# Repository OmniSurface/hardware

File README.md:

This repo stores hardware design files and datasheets of components we used.

## Files
- `datasheet`: this folder stores datasheets of the ICs/sensors we used.
- `img`: pictures of circuit diagrams
- `kicad components`: stores schematic files and footprints of components
- `tlv2771 breakout`: an easy breakout board for the breadboard testing of the TLV2771 Operational Amplifier chip.
- `piezo_v1`: version 1 of the integrated circuit, including a piezo sensor, preamplification of the sensor reading, and a high sampling rate ADC circuit, which communicates with the MCU (ESP32S3) using the SPI interface.
- `mini_v1`: deleted ADC subcircuit and uses a dual channel amplifier (TLV2722) to amplify readings from both the piezo and bone conducting mic sensor. Uses CR2477 coin cell battery to power the ESP32S3 XIAO.
- `mini_lipo_v1`: same as the `mini_v1`, other than it uses a 30.0mm x 25.5mm x 7.1mm 500mAh lipo battery to power the ESP32S3 XIAO.
- `backup_microphone`: this file includes the testing for the backup plan, which is using microphone as the second sensor if piezo or bone conduction cannot work as expected.

## Circuit Diagrams
### Preamplifier 

- `Vcc` uses 3.3v from the ESP32S3.
- `Rb` = 10MOhm
- `Rg` = 1kOhm
- `Rf` = 56kOhm
- `Cf` is not used, since we want to keep the high-frequency signals.
- `1/2 Vcc` is created using a voltage divider (2 x 10kOhm resistor).

### ADC 

With some modifications:
- `IN+` of the ADC is connected to the `Vo` of the preamplifier.
- `IN-` of the ADC is connected to `1/2 Vcc`.
- `V+` line and the `VIO` are connected to the 3.3v from the ESP32S3.
- `VREF` = 3v. This means the ADC can convert voltage from -3v to 3v. In our configuration, however, we will only generate signals from -1/2 Vcc to 1/2 Vcc, which is around -1.65v to 1.65v. This will waste 1-bit resolution of the ADC as we only use half of the voltage range. Hope it could still be accurate enough, or we can develop a differential input for the ADC (rather than directly pulling 1/2 Vcc to the `IN-` of the ADC).

## Main Considerations
### Bandwidth
In our preliminary testing using o-scope, a gain of around 50x can produce a desirable signal for all kinds of surface interactions. The TLV2771 amplifier we used has a Gain Bandwidth (GBW) of 5.1 MHz. The formula to calculate the bandwidth of the op-amp when operating at a specific gain is given by:
\[ \text{Bandwidth} = \frac{\text{GBW}}{\text{Gain}} \]
Where,
    - Bandwidth is the frequency at which the gain of the op-amp falls to 1 (unity gain) when operating at a specific gain setting.
    - GBW (Gain-Bandwidth Product) is a characteristic of the op-amp and is usually specified in the datasheet. It's the product of the bandwidth and the gain at which the bandwidth is measured.
    - Gain is the amplification factor at which the op-amp is operating.

In our case, the gain is 50, then the bandwidth is around 100kHz, which could be sufficient in our case of interacting with surfaces.

If a higher GBW turns out to be necessary, we can use LMP7732, which has a GBW of __22MHz__.

### ADC sampling
The AD4022 chip we used for ADC has a maximum sampling rate of around 500kSPS. 

According to the Nyquist theorem, which states that to avoid aliasing, which is the distortion that occurs when the signal is undersampled, the sampling rate must be at least twice the highest frequency present in the signal. This minimum sampling rate is known as the Nyquist rate.
\[ f_{\text{Nyquist}} = 2 \times f_{\text{max}} \]
Where,
 - $f_{\text{max}}$ is the highest frequency component in the signal.

 Given the bandwidth of the preamplifier is 100kHz, our 500kHz sampling rate could be sufficient.

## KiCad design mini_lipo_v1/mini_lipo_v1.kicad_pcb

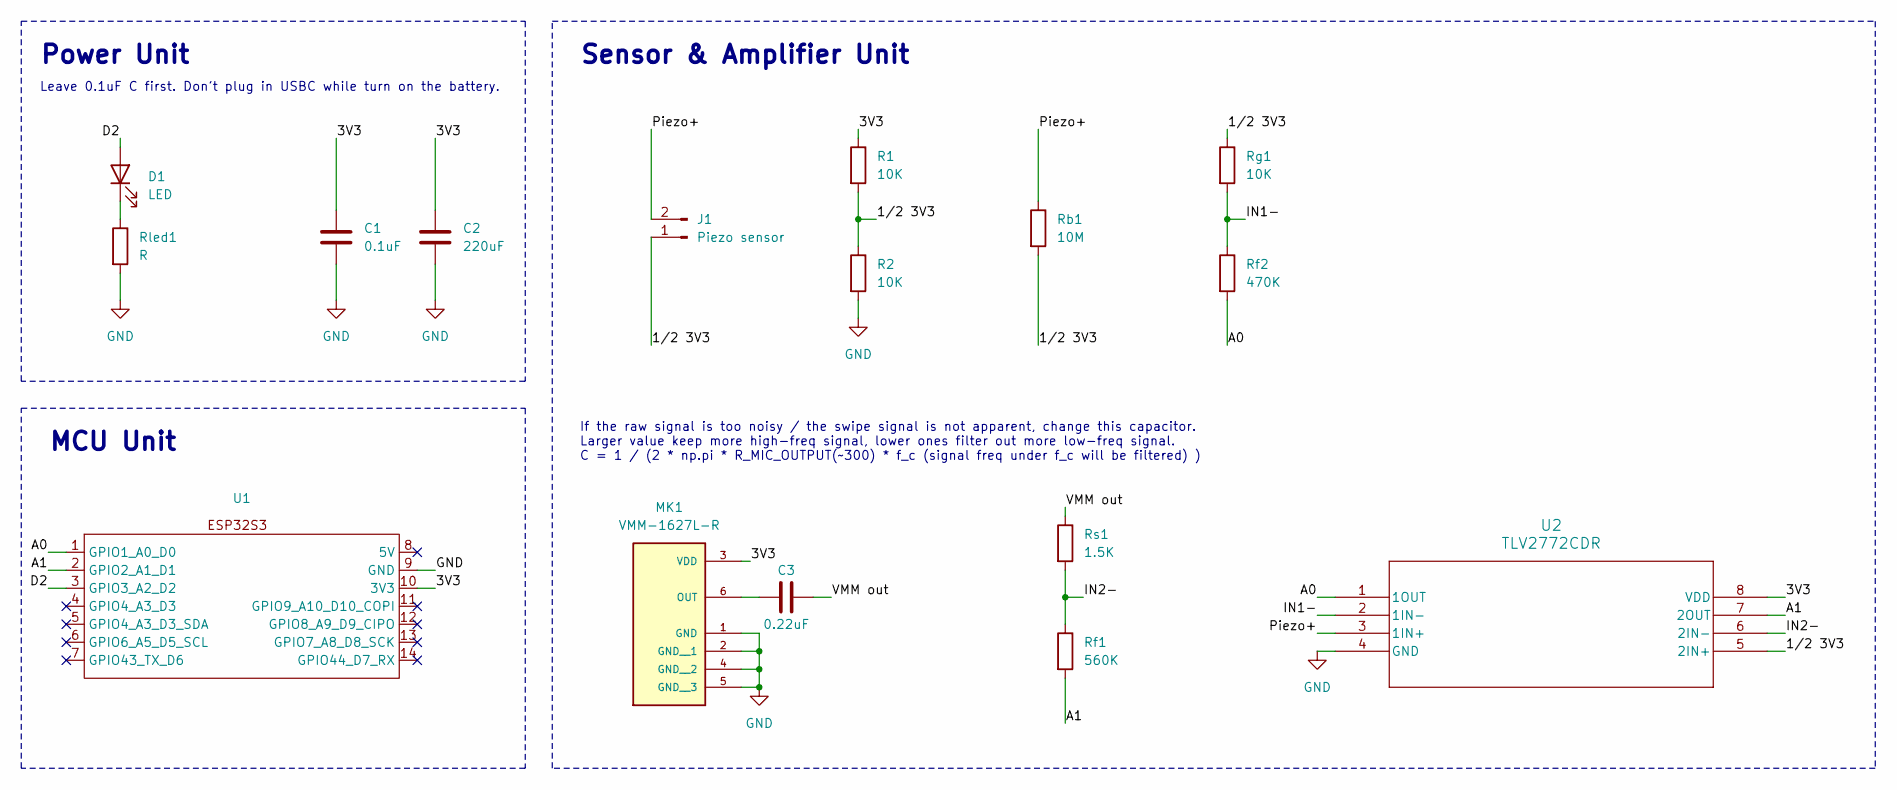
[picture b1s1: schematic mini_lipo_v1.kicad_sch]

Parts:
C1: 0.1uF; C_0805_2012Metric_Pad1.18x1.45mm_HandSolder
C2: 220uF; 300uF_laydown
C3: 0.22uF; C_0805_2012Metric_Pad1.18x1.45mm_HandSolder
D1: LED; LED_D3.0mm
J1: Piezo sensor; PinHeader_1x02_P2.54mm_Vertical
MK1: VMM-1627L-R; MIC_VMM-1627L-R; PARTREV A
R1, R2: 10K; R_0805_2012Metric_Pad1.20x1.40mm_HandSolder
Rb1: 10M; R_0805_2012Metric_Pad1.20x1.40mm_HandSolder
Rf1: 560K; R_0805_2012Metric_Pad1.20x1.40mm_HandSolder
Rf2: 470K; R_0805_2012Metric_Pad1.20x1.40mm_HandSolder
Rg1: 10K; R_0805_2012Metric_Pad1.20x1.40mm_HandSolder
Rled1: R; C_0805_2012Metric_Pad1.18x1.45mm_HandSolder
Rs1: 1.5K; R_0805_2012Metric_Pad1.20x1.40mm_HandSolder
U1: XIAO_SMD
U2: TLV2772CDR

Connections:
/1/2 3V3: J1.1, R1.2, R2.1, Rb1.2, Rg1.1, U2.5 (2IN+)
/3V3: C1.1, C2.1, MK1.3 (VDD), R1.1, U1.10 (3V3), U2.8 (VDD)
/A0: Rf2.2, U1.1 (GPIO1_A0_D0), U2.1 (1OUT)
/A1: Rf1.2, U1.2 (GPIO2_A1_D1), U2.7 (2OUT)
/D2: D1.2 (A), U1.3 (GPIO3_A2_D2)
/IN1-: Rf2.1, Rg1.2, U2.2 (1IN-)
/IN2-: Rf1.1, Rs1.2, U2.6 (2IN-)
/Piezo+: J1.2, Rb1.1, U2.3 (1IN+)
/VMM out: C3.2, Rs1.1
GND: C1.2, C2.2, MK1.1 (GND), MK1.2 (GND__1), MK1.4 (GND__2), MK1.5 (GND__3), R2.2, Rled1.2, U1.9 (GND), U2.4 (GND)
unnamed: D1.1 (K), Rled1.1
unnamed: C3.1, MK1.6 (OUT)

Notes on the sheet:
Power Unit
Sensor & Amplifier Unit
If the raw signal is too noisy / the swipe signal is not apparent, change this capacitor. Larger value keep more high-freq signal, lower ones filter out more low-freq signal. C = 1 / (2 * np.pi * R_MIC_OUTPUT(~300) * f_c (signal freq under f_c will be filtered) )
MCU Unit
Leave 0.1uF C first. Don't plug in USBC while turn on the battery.

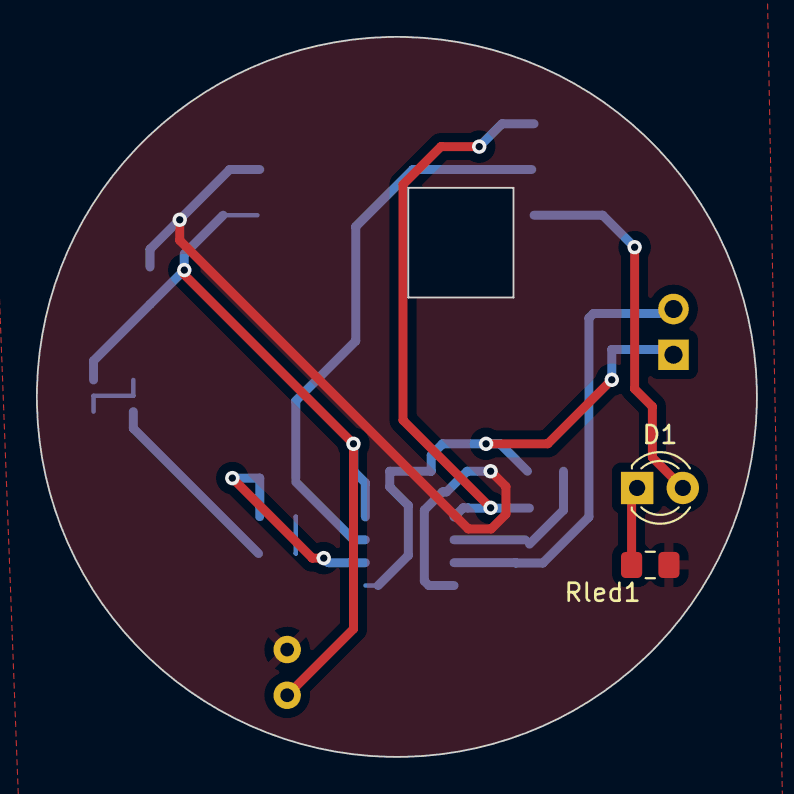
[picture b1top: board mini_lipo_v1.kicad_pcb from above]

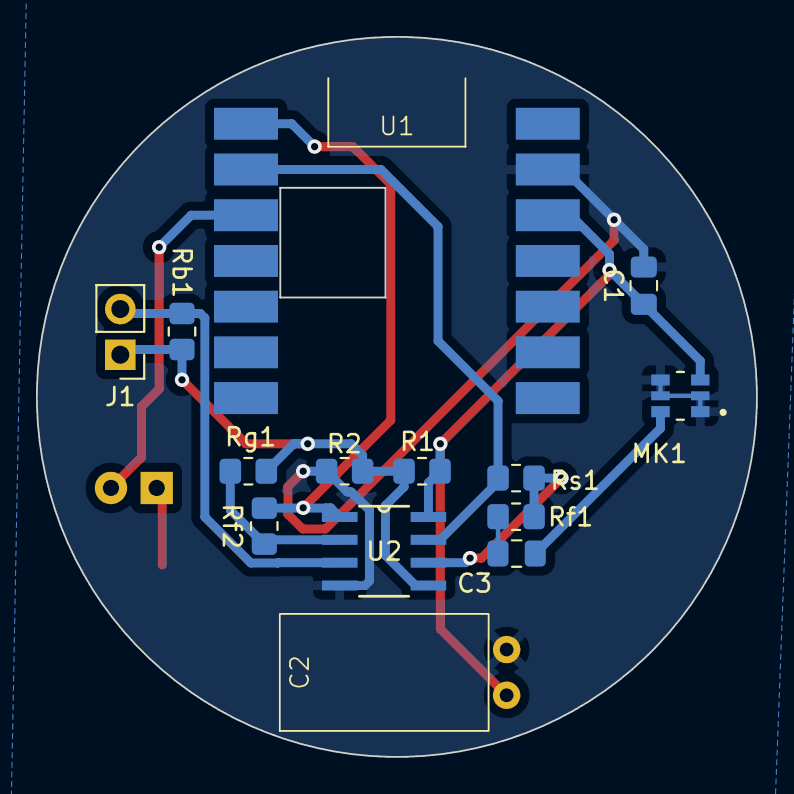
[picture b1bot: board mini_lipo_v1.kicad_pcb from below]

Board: 2 copper layers, 40.0 x 40.0 mm, 16 parts (14 on the bottom side), 12 nets.

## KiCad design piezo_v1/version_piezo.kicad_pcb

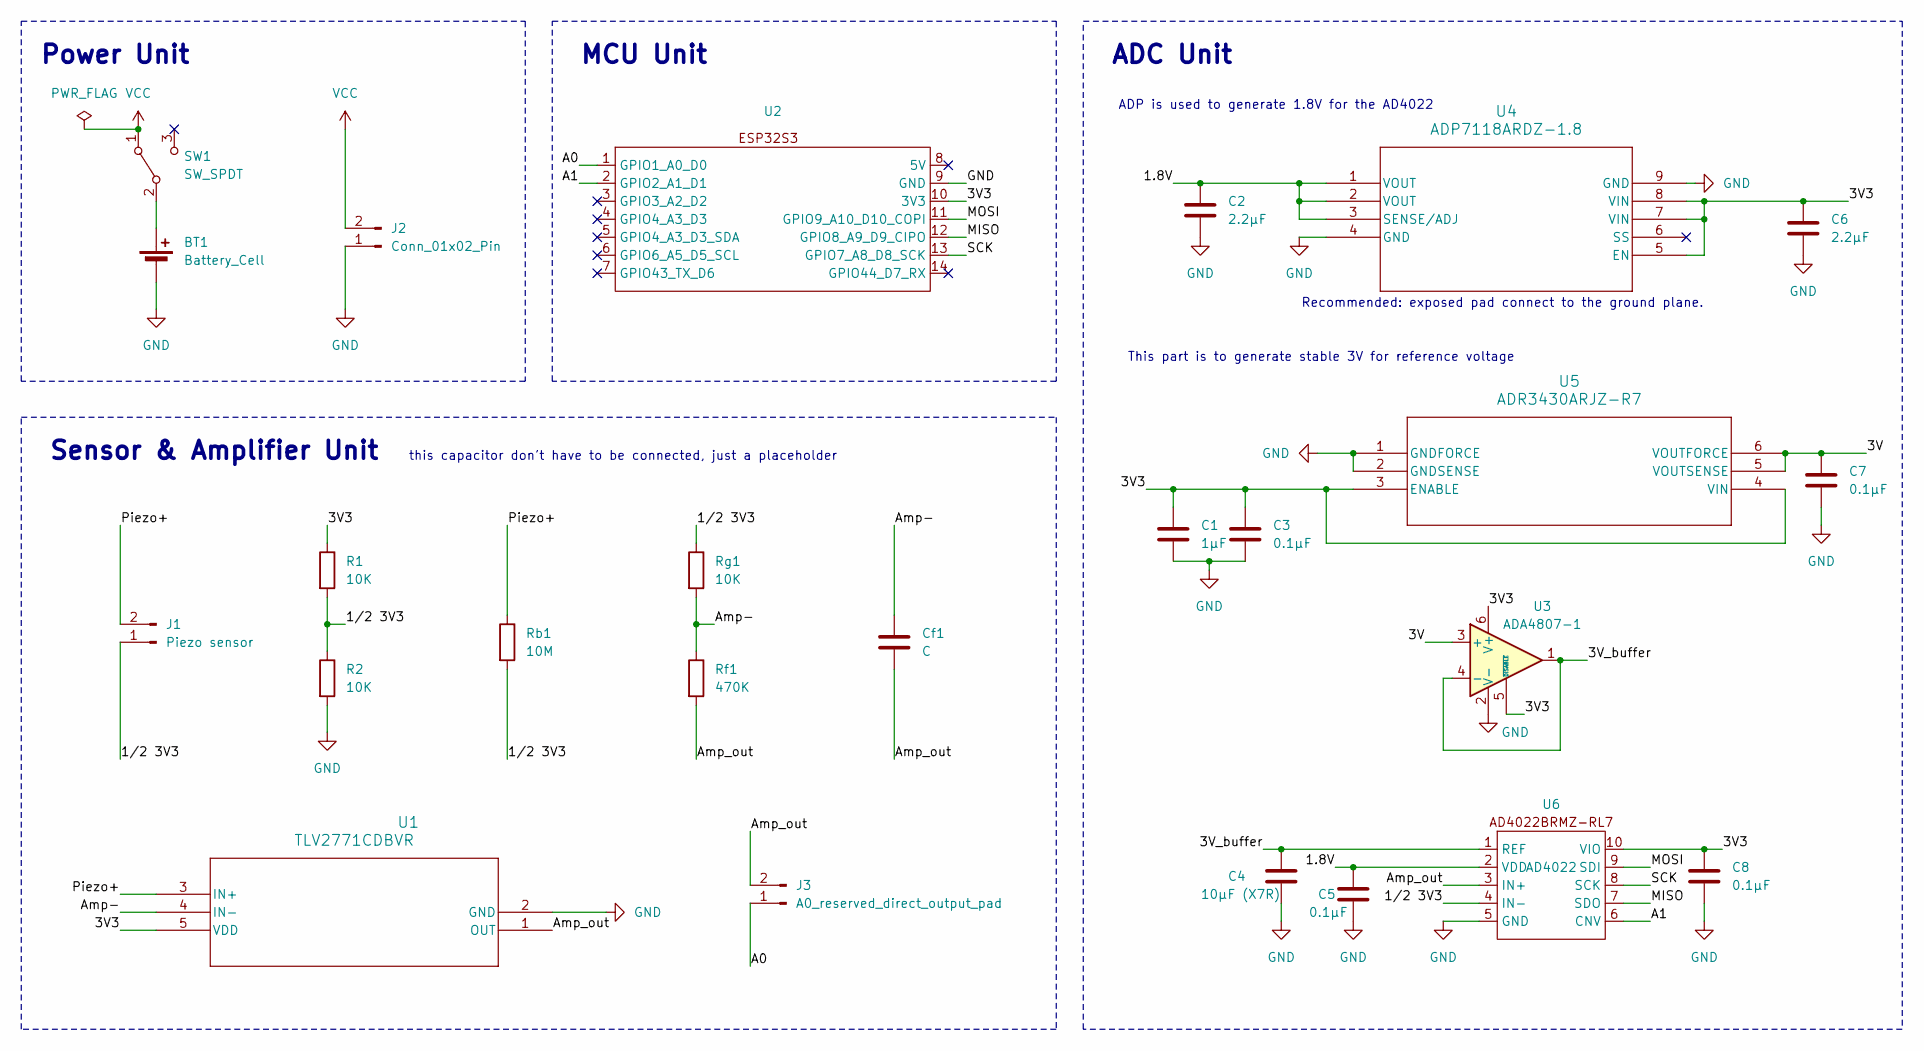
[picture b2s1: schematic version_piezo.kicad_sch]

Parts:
BT1: Battery_Cell; JST_ZE_SM02B-ZESS-TB_1x02-1MP_P1.50mm_Horizontal
C1: 1μF; C_0805_2012Metric_Pad1.18x1.45mm_HandSolder
C2, C6: 2.2μF; C_0805_2012Metric_Pad1.18x1.45mm_HandSolder
C3, C5, C7, C8: 0.1μF; C_0805_2012Metric_Pad1.18x1.45mm_HandSolder
C4: 10μF (X7R); C_0805_2012Metric_Pad1.18x1.45mm_HandSolder
Cf1: C; C_0805_2012Metric_Pad1.18x1.45mm_HandSolder
J1: Piezo sensor; PinHeader_1x02_P2.54mm_Vertical
J2: Conn_01x02_Pin; LED_D5.0mm
J3: A0_reserved_direct_output_pad; R_0805_2012Metric_Pad1.20x1.40mm_HandSolder
R1, R2: 10K; R_0805_2012Metric_Pad1.20x1.40mm_HandSolder
Rb1: 10M; R_0805_2012Metric_Pad1.20x1.40mm_HandSolder
Rf1: 470K; R_0805_2012Metric_Pad1.20x1.40mm_HandSolder
Rg1: 10K; R_0805_2012Metric_Pad1.20x1.40mm_HandSolder
SW1: SW_SPDT; SWITCH_THT_SPDT_11MA1QS1
U1: TLV2771CDBVR
U2: XIAO_ESP32_SENSE
U3: ADA4807-1; SOT-23-6
U4: ADP7118ARDZ-1.8; SOIC-8-1EP_3.9x4.9mm_P1.27mm_EP2.41x3.81mm
U5: ADR3430ARJZ-R7; SOT-23-6
U6: AD4022; MSOP-10-1EP_3x3mm_P0.5mm_EP1.68x1.88mm

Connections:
/1.8V: C2.1, C5.1, U4.1 (VOUT), U4.2 (VOUT), U4.3 (SENSE/ADJ), U6.2 (VDD)
/1/2 3V3: J1.1, R1.2, R2.1, Rb1.2, Rg1.1, U6.4 (IN-)
/3V: C7.1, U3.3 (+), U5.5 (VOUTSENSE), U5.6 (VOUTFORCE)
/3V3: C1.1, C3.1, C6.1, C8.1, R1.1, U1.5 (VDD), U2.10 (3V3), U3.5 (~DISABLE), U3.6 (V+), U4.5 (EN), U4.7 (VIN), U4.8 (VIN), U5.3 (ENABLE), U5.4 (VIN), U6.10 (VIO)
/3V_buffer: C4.1, U3.1, U3.4 (-), U6.1 (REF)
/A0: J3.1, U2.1 (GPIO1_A0_D0)
/A1: U2.2 (GPIO2_A1_D1), U6.6 (CNV)
/Amp-: Cf1.1, Rf1.1, Rg1.2, U1.4 (IN-)
/Amp_out: Cf1.2, J3.2, Rf1.2, U1.1 (OUT), U6.3 (IN+)
/MISO: U2.12 (GPIO8_A9_D9_CIPO), U6.7 (SDO)
/MOSI: U2.11 (GPIO9_A10_D10_COPI), U6.9 (SDI)
/Piezo+: J1.2, Rb1.1, U1.3 (IN+)
/SCK: U2.13 (GPIO7_A8_D8_SCK), U6.8 (SCK)
GND: BT1.2 (-), C1.2, C2.2, C3.2, C4.2, C5.2, C6.2, C7.2, C8.2, J2.1, R2.2, U1.2 (GND), U2.9 (GND), U3.2 (V-), U4.4 (GND), U4.9 (GND), U5.1 (GNDFORCE), U5.2 (GNDSENSE), U6.5 (GND)
unnamed: BT1.1 (+), SW1.2 (B)
VCC: J2.2, SW1.1 (A)

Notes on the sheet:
Power Unit
Sensor & Amplifier Unit
ADC Unit
this capacitor don't have to be connected, just a placeholder
This part is to generate stable 3V for reference voltage
Recommended: exposed pad connect to the ground plane.
MCU Unit
ADP is used to generate 1.8V for the AD4022

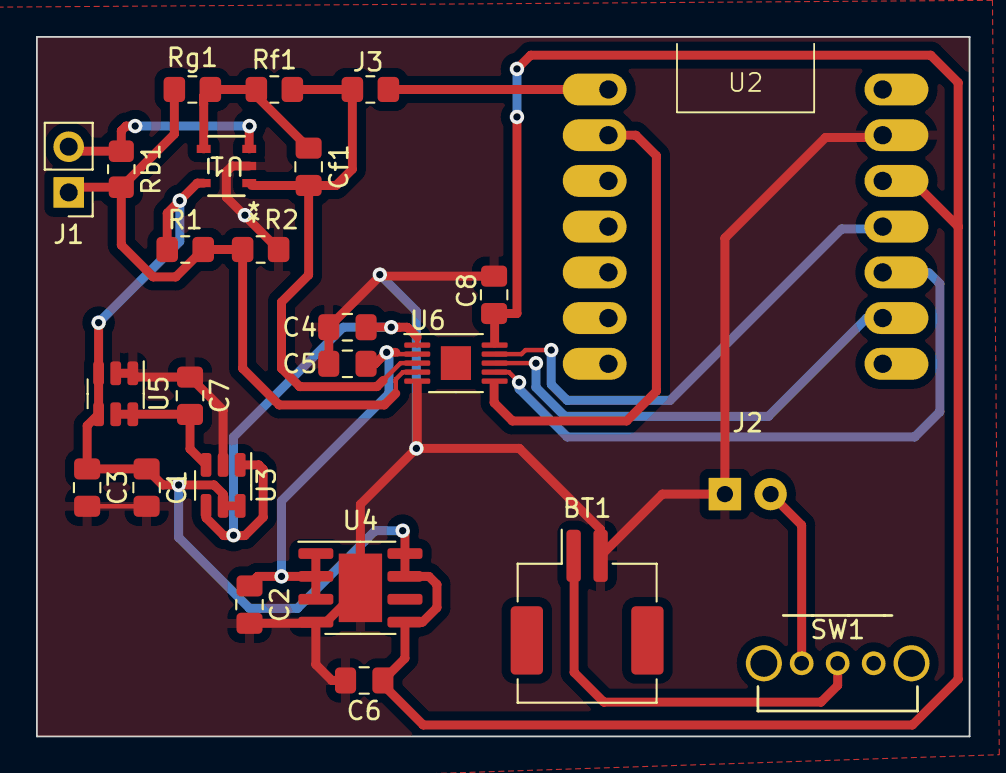
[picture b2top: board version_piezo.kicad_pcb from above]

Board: 2 copper layers, 51.8 x 38.9 mm, 25 parts (0 on the bottom side), 16 nets.

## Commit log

2024-04-19 datasheet update
2024-04-19 esp datasheet
2024-04-19 add backup plan info
2024-05-09 kicad
2024-05-09 readme
